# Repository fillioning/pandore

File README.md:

# Pandore

**Open-source digital audio instrument prototyping platform.**

Pandore is a custom-designed PCB built around the [LattePanda Mu](https://www.lattepanda.com/lattepanda-mu) compute module, a [Teensy 4.1](https://www.pjrc.com/store/teensy41.html) audio bridge, dual [RP2350](https://www.raspberrypi.com/products/rp2350/) microcontrollers, and a professional audio I/O chain. It provides a complete hardware foundation for building digital audio instruments, effects processors, and experimental sound tools.

## Status

**Revision A0** — PCBs fabricated (3 units). Manufacturing files released 2026-03-19. DRC passing, all components sourced.

> **PCBWay substitution:** RP2350A was unavailable at assembly time; PCBWay substituted **RP2350B (QFN-80)** for both MCU positions. RP2350A and RP2350B are binary-compatible — same cores, same peripherals, same memory map — they differ only in package size and number of exposed GPIO pins (30 vs 48). Firmware developed on RP2350A Pico boards transfers without modification.

## Board Specifications

| Parameter | Value |
|---|---|
| **Dimensions** | 260 mm x 110 mm |
| **Layers** | 4 (F.Cu / In1 / In2 / B.Cu) |
| **Components** | 804 (141 unique part numbers) |
| **Vias** | 2,217 |
| **Design tool** | KiCad 10 |

## Architecture

```
                         +-----------------+
                         |  LattePanda Mu  |
                         |  (x86-64 SBC)   |
                         +--------+--------+
                                  |
          +----------+-----------+-----------+----------+
          |          |                       |          |
 +--------+-------+  |             +---------+--------+ |
 |  RTIO MCU      |  |             |  Management MCU  | |
 |  (RP2350)      |  |             |  (RP2350)        | |
 +--------+-------+  |             +---------+--------+ |
          |          |                       |          |
 +--------+-------+  |             +---------+--------+ |
 | UART, SPI, I2C |  |             | GPIO, Power Seq, | |
 | ADC, 8x PWM    |  |             | Fan, Display     | |
 +----------------+  |             +------------------+ |
                     |                                  |
            +--------+--------+                         |
            |   Teensy 4.1    |                         |
            | (I2S-to-USB     |                         |
            |  Audio Bridge)  |                         |
            +--------+--------+                         |
                     |                                  |
            +--------+--------+               +---------+--------+
            |   CS4272 Codec  |               |   Boot, BIOS,    |
            |   (24-bit I2S)  |               |   Ethernet, M.2  |
            +-----------------+               +------------------+
```

### Compute

- **LattePanda Mu** — x86-64 SBC (Intel N100 or N305), main application processor. Recommended: DFR1147 (N100, 16 GB LPDDR5) — the N305 gives only ~13% single-core gain at ~2× cost, with no meaningful benefit for real-time audio workloads where single-thread performance dominates.
- **RTIO MCU (RP2350)** — Real-time I/O: UART, SPI, I2C, USB, ADC, 8x PWM channels
- **Management MCU (RP2350)** — System control: power sequencing, GPIO, fan, display, boot

### Audio

- **Audio/MIDI bridge:** [Teensy 4.1](https://www.pjrc.com/store/teensy41.html) — I2S-to-USB audio bridge between the CS4272 codec and the LattePanda Mu, also handles MIDI data transfer to the host computer
- **Codec:** Cirrus Logic CS4272 — stereo 24-bit ADC/DAC, I2S interface
- **Preamp:** THS4521 fully-differential amplifier + OPA1656 op-amp signal conditioning
- **Phantom power:** 48V supply via TI LM5158 flyback controller + TPS7A4001 ultra-low-noise 40V LDO post-regulation (~10 mA) for condenser microphones
- **I2S isolation:** TI ISO7762FDBQR — 6-channel digital isolator (4 forward / 2 reverse), 100 Mbps, 5000 VRMS galvanic isolation between digital and audio domains
- **I2C isolation:** TI ISO1640BDR — isolated I2C for codec control path, 2500 VRMS isolation
- **Isolated power:** Murata NXE2S1212MC — 1W isolated 12V→12V DC/DC converter for the isolated audio domain
- **MIDI isolation:** Isocom H11L1SMT optoisolator with Schmitt-trigger output on MIDI IN
- **Monitor output:** Dedicated headphone/speaker amplifier with hardware volume knob (Bourns PTR902-2020K-A103 — 10 kΩ audio taper, 20 mm shaft)
- **Input buffering:** Balanced input stage with line/mic switching
- **Output buffering:** Line-level outputs

### Power

| Rail | Voltage | Current | Purpose |
|---|---|---|---|
| 12V | Main input | LattePanda Mu, OLED drive |
| 5V | 2A (10W) | Digital logic, USB peripherals |
| 3.3V | 3A (10W) | MCUs, codec digital, I/O |
| 48V | 10 mA | Condenser microphone phantom power |
| AV5 / AV3P3 | — | Analog audio supply (isolated domain) |
| VSTBY | ~3.3V | Standby (CR2032 backup) |

**Power ICs:**

| Part | Role |
|---|---|
| Diodes AP63356Q (×2) | Synchronous buck converters (3.5A), main DC-DC regulation |
| STM LDL212DR (×3) | Ultra-low-dropout LDOs, local clean rails |
| ETEK ET20162 (×5) | Per-rail 5V load switching, 1A each |
| TI LM5158RTER | Flyback controller for 48V phantom supply |
| TI TPS7A4001DGNR | Ultra-low-noise 40V LDO, phantom post-regulation |
| Murata NXE2S1212MC | 1W isolated 12V DC/DC for audio analog domain |

- Reverse-polarity, overcurrent, and overvoltage protection
- PTC fuses (Bel Fuse) on USB VBUS
- Managed power-on sequencing via Management MCU

### Connectivity

- **Ethernet** — 2× Gigabit Ethernet via Realtek RTL8111H-CG PCIe controllers (U7, U8), 2× shielded RJ45 with isolation transformers (Würth 749020111A)
- **USB** — 8× USB from LattePanda Mu (3× USB 3.0 + 5× USB 2.0); 2× USB-C receptacles for Teensy 4.1 bridge
- **MIDI** — 5-pin DIN IN/OUT with H11L1 optoisolation
- **Display** — 24-pin 0.5mm FPC ZIF connector (GCT FFC2A32-24-T) for OLED status display (SSD1309, 128×64 px, 1.54") — see [Components Requiring Separate Assembly](#components-requiring-separate-assembly)
- **M.2 Key-M** — PCIe x4 (NVMe SSD)
- **M.2 Key-A+E** — WiFi/Bluetooth (tested: Intel AX210 — WiFi 6E tri-band + BT 5.3) or alternate storage
- **Expansion headers** — GPIO, analog, I/O breakouts; 2× Grove I2C connectors; I2S header; UART debug

### User Interface

- **Encoder:** Bourns PEL12T-4225T-S1024 — 24 PPR optical rotary encoder with momentary push switch and RGB LED illumination
- **Tactile switches:** 4× C&K PTS810 momentary switches (B1–B4)
- **Volume knob:** Bourns PTR902-2015K-B103 potentiometer (monitor output level)
- **RGBA LED:** AMS-OSRAM multi-colour LEDs — blue (×3), green (×4), orange (×7), red (×1) status/indicator outputs

### Sensors

- **BMI270** — 6-axis IMU (accelerometer + gyroscope) for motion-based control

### Flash Storage

3× Winbond W25Q128JVSIM (128 Mbit / 16 MB, QSPI):
- U2 — BIOS flash (LattePanda Mu)
- U5 — RTIO MCU flash (RP2350, U3)
- U6 — Management MCU flash (RP2350, U4)

### Thermal

- PWM-controlled fan driver circuit
- Three heatsink options: active cooler, thin passive, fanless

## Audio Performance

See **[Audio Performance](AUDIO_PERFORMANCE.md)** for the full signal chain, component specs, system-level estimates, physical I/O, and performance class.

**Highlights:** 24-bit / 192 kHz, 114 dB dynamic range, -100 dB THD+N, 5000 VRMS galvanic isolation, 2× Neutrik combo XLR+TRS inputs with 48V phantom power.

## Repository Structure

```
pandore/
  hw/               Schematics (.kicad_sch) and PCB layout (.kicad_pcb)
  doc/
    arch/           Architecture diagrams (draw.io)
    img/            Board renders
    reference/      Datasheets, app notes, design guides (PDF)
  lib/              3D models (.step), KiCad symbols and footprints
  release/          Manufacturing artifacts (Gerbers, BOM, placement, 3D)
```

### Schematic Hierarchy

The top-level schematic (`pandore.kicad_sch`) references 24 sub-sheets organized by subsystem:

**Audio** — `audio`, `audio-codec`, `audio-inputs`, `audio-inbuf`, `audio-outputs`, `audio-outbuf`, `audio-isolation`, `audio-monitor`, `audio-power`

**Compute** — `computer`, `cpumod`, `mcu`, `mgmtmcu`, `rtmcu`

**Power** — `power`, `audio-power`

**Interface** — `eth`, `usbport`, `midi`, `display`, `extraport`, `mdot2`

**System** — `bootctl`, `bios`, `fan`

## Components Requiring Separate Assembly

The PCBWay PCBA order covers all SMD components. The following through-hole and DNP parts must be sourced and hand-soldered separately. BOM part numbers are listed; substitutions are noted where a different part is recommended over the original BOM.

| BOM# | Per board | Ref | Description | Part (installed) | Notes |
|------|-----------|-----|-------------|-----------------|-------|
| 40 | 1 | E1 | Encoder + RGB LED + switch | Bourns **PEL12T-4225T-S1024** | 24 PPR, push switch, RGB illuminated |
| 47 | 2 | J4, J5 | Mic/Line input combo jack | Neutrik **NCJ9FI-H-0** | XLR + 6.35mm TRS + 3-way switch |
| 50 | 2 | J8, J9 | Ethernet RJ45 | Amphenol **RJE58-188-5411** | 8P8C shielded, dual LEDs, Cat5e |
| 51 | 2 | J10, J11 | MIDI DIN | Same Sky **SDS-50J** | 5-pin DIN 180° |
| 52 | 1 | J12 | Line output TRS | Neutrik **NSJ12HF-1** | 6.35mm stacking stereo |
| 55 | 2 | J15, J16 | GPIO expansion header | Samtec **MTSW-108-22-L-T-330-RA** | 3×8 right-angle, 2.54mm pitch |
| 56 | 2 | J17, J18 | Grove connectors | TE **440055-4** | HPI 2.0mm R/A THT (replaces BOM 2041145-4, same family) |
| 105 | 1 | R273 | Headphone volume pot | Bourns **PTR902-2020K-A103** | Audio taper, 20mm shaft (replaces BOM 2015K-B103, linear, 15mm) |
| — | 1 | J25 | OLED display panel | **Microtips REX012864AYAP3N00000** (primary) or Midas MCOT128064B1V-WM (alt) | SSD1309, 128×64, 24-pin 0.5mm FPC; J25 ZIF socket is PCBWay-assembled |
| — | 1 | J28/J29 | Audio/MIDI bridge module | **PJRC Teensy 4.1** | J28/J29 USB-C receptacles are PCBWay-assembled |
| — | 1 | J13 | NVMe SSD | User choice | M.2 2280 Key-M, PCIe x4 |
| — | 1 | J19 | WiFi/BT module | **Intel AX210** (WiFi 6E + BT 5.3) | M.2 2230 Key-E |

---

## Manufacturing

The `release/` directory contains two packages dated 2026-03-19 (revision A0):

- **`pandore_*_A0_pcba.zip`** — PCBA package: Gerbers, drill files, BOM (.csv), pick-and-place (.pos)
- **`pandore_*_A0_release.zip`** — Full release: PCBA files + 3D assembly model (.step), assembly drawings (PDF), rendered board images, ERC/DRC reports

4-layer stackup. 2,439 drill holes. All components have manufacturer part numbers assigned.

## Reference Documentation

The `doc/reference/` directory includes datasheets and design guides used during development:

- RP2350 datasheet and hardware design guide
- LattePanda Mu evaluation kit guide and carrier board reference
- CS4272 codec (via SuperAudioBoard design guide and schematic)
- THAT1512 microphone preamp gain configuration (reference design)
- 48V phantom power supply design (TI SBOA320A + ultra-low-noise RAQ approach)
- Analog circuit design references (Analog Secrets series, AES mic preamp paper)
- THAT Corporation mic preamp reference design (git submodule)

## Requirements

- [KiCad 10](https://www.kicad.org/) to open and edit schematics and PCB layout
- [draw.io](https://app.diagrams.net/) to view architecture diagrams

## Credits

Designed by **Vincent Fillion** at [Artificiel](https://artificiel.org), with the help of **Alexandre Burton**.

Hardware engineering and KiCad source files by **Laurence Deschênes Villeneuve** ([@laurencedv](https://github.com/laurencedv)).

## License

This project is licensed under the [CERN Open Hardware Licence Version 2 — Strongly Reciprocal (CERN-OHL-S-2.0)](https://ohwr.org/cern_ohl_s_v2.txt).

You are free to use, study, modify, and distribute this design, provided that:
- You credit the original authors
- You distribute any modified versions under the same licence
- You make the source files available

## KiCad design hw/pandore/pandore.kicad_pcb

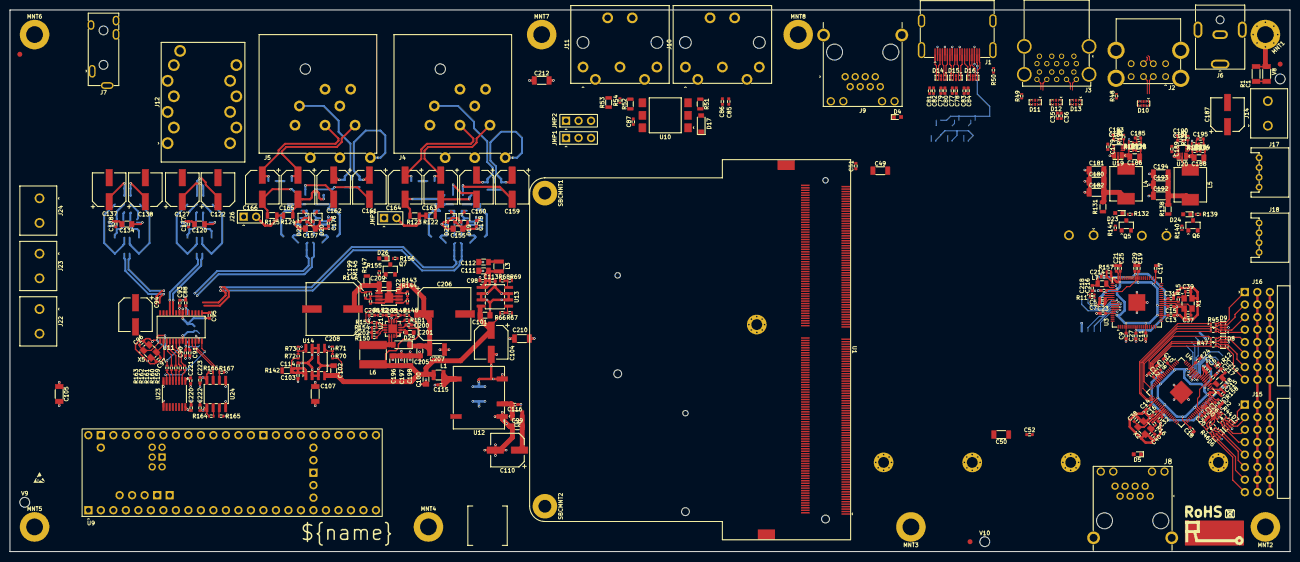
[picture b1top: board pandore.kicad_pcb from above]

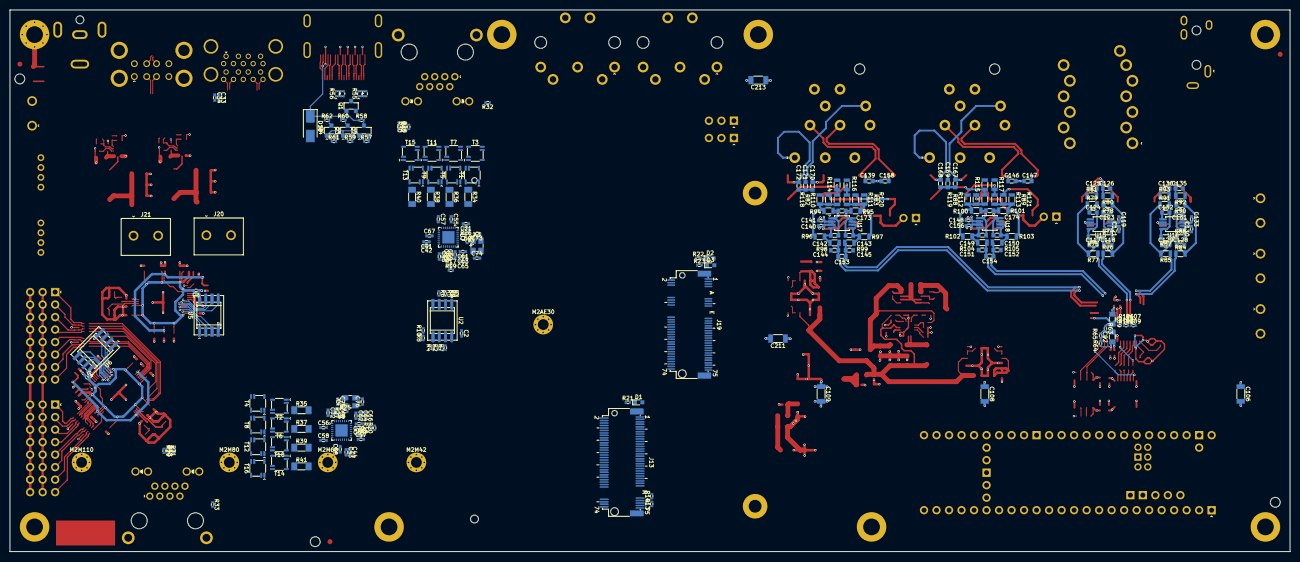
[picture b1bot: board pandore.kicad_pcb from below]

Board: 4 copper layers, 260.0 x 110.0 mm, 530 parts (227 on the bottom side), 432 nets.

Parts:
C1: 10nF, 630V, X7R; CAPC3216
C2, C3, C4, C5, C6, C7, C8, C9, C10, C11, C12, C13, C14, C15, C16, C17, C18, C19, C20, C21, C22, C23, C24, C25, C26, C27, C28, C29, C30, C33, C34, C35, C36, C41, C42, C43, C44, C45, C46, C47, C48, C51, C52, C53, C54, C55, C56, C57, C58, C59, C60, C61, C62, C67, C68, C69, C70, C71, C72, C77, C78, C79, C80, C81, C82, C83, C84, C85, C86, C87, C88, C90, C91, C93, C95, C113, C114, C119, C133, C140, C156, C175, C176, C177, C178, C179, C189, C220, C221, C222, C223: 100nF, 16V, X7R; CAPC1005
C31, C32, C63, C64, C65, C66, C98, C103, C214, C215, C216, C217, C218, C219: 4.7µF, 6.3V, X5R; CAPC1005
C37, C38, C39, C40: 15pF, 6.3V, X7R; CAPC1005
C49, C50: 1nF, 1000V, X7R; CAPC3216
C73, C74, C75, C76, C96, C97: 12pF, 6.3V, X7R; CAPC1005
C89, C92: 10µF, 16V, X5R; CAPC2012
C94, C104, C110: 47µF, 25V, 20%; CAPAE630Xxxx
C99, C100, C101, C102, C111, C112, C120, C134, C155, C157, C186, C188, C196, C197, C198: 10µF, 25V, X5R; CAPC2012
C105, C106, C107, C108, C109, C210, C211, C212, C213: 100pF, 1kV, X5R; CAPC3216
C115, C116, C200: 100nF, 25V, X7R; CAPC1005
C117, C118, C128, C129: 1.3nF, 16V, C0G; CAPC1608
C121, C130, C141, C148: 220nF, 16V, X7R; CAPC1005
C122, C127, C137, C138, C159, C160, C161, C162, C187: 100µF, 25V, 20%; CAPAE630Xxxx
C123, C124, C131, C132: 300pF, 16V, C0G; CAPC1608
C125, C126, C135, C136: 33nF, 16V, C0G; CAPC1608
C139, C144, C145, C146, C147, C151, C152, C158, C167, C168, C169, C170, C171, C172, C173, C174: 100pF, 50V, C0G; CAPC1608
C142, C143, C149, C150: 1nF, 16V, C0G; CAPC1608
C153, C154: 2.7nF, 16V, C0G; CAPC1608
C163, C164, C165, C166: 47µF, 100V, 20%; CAPAE630Xxxx
C180, C181, C182, C192, C193, C194: 22µF, 25V, X5R; CAPC3216
C183, C190, C204: 1nF, 16V, X7R; CAPC1005
C184, C191: 68pF, 10V, X7R; CAPC1005
C185, C195: 47pF, 10V, X7R; CAPC1005
C199: 10nF, 100V, X7R; CAPC1005
C201: 1µF, 16V, X7R; CAPC1608
C202: 12nF, 16V, X7R; CAPC1005
C203: 1pF, 16V, X7R; CAPC1005
C205, C209: 100nF, 100V, X7R; CAPC2012
C206, C208: 56µF, 100V, 20%; CAPAE1000Xxxx
C207: 10µF, 100V, X5R; CAPC3225
D1, D2, D3, D4, D5, D23, D24, D26: green; LEDM1608X80
D6, D7, D8, D9, D10, D11, D12, D13, D14, D15, D16: 5V; DFN50P100X250X55-10_ESD204
D17: 75V, 150mA, 1V@100mA; sod-123
D18: 40V, 3A, 500mV@3A; dio_sma
D19, D20, D21, D22: 75V, 140mA, 1.25V@150mA; SOT65P210X90-3
D25: 100V, 150mA, 450mV@10mA; sod-123
J1: HDMI; te_1747981-1
J2: USB2-A_2stacked; USB2_A_RCPT_HORZ_2STACKED
J3: USB3-A_2stacked; USB3_A_RCPT_HORZ_2STACKED
J4, J5: XLR+TRS6.35+3SW; neutrik_ncj9fi-h-0
J6: VIN; samesky_PJ-063BH
J7: TRS; samesky_SJ3-3508x
J8, J9: 8p8c_2led_shield; amphenol_RJE58-188-54x1-0x
J10: MIDI_in; samesky_SDS-50J
J11: MIDI_out; samesky_SDS-50J
J12: TRS; neutrik_nsj12hf-1
J13: NGFF_M.2_M; NGFF_M.2_CONN
J14: VIN; Wurth_691137710002
J15: AIO; HDR254P3X8-THRA
J16: DIO; HDR254P3X8-THRA
J17, J18: GROVE; te_2041145-4
J19: NGFF_M.2_AE; NGFF_M.2_CONN
J20: V5; Wurth_691137710002
J21: V3.3; Wurth_691137710002
J22: V12ISO; Wurth_691137710002
J23: AV5; Wurth_691137710002
J24: AV3P3; Wurth_691137710002
J26: PPWR; HDR254P1X02-TH
JMP1: MIDIRX; HDR254P1X03-TH
JMP2: MIDITX; HDR254P1X03-TH
JMP3: PPWR; HDR254P1X02-TH
L1, L2, L3: 10µH; INDC2520
L4, L5: 8.2µH, 5A; Eaton_HPAL1V0630
L6: Ind; WE_IND5030
L7, L8: 3.3µH, 1.8A; INDC2012
M2AE30, M2M42, M2M60, M2M80, M2M110: M2; mnt_M2_ele
MNT1: MNT-CHASSIS; mnt_M3_ele
MNT2, MNT3, MNT4, MNT5, MNT6, MNT7, MNT8: Mounting; mnt_M3
Q1, Q2, Q3, Q4, Q5, Q6, Q7: MOSFET_EN-N; SOT95P280X100-3
R1: 1MΩ, 5%, 250mW; RESC3216
R2, R3, R4, R5, R6, R7: 0, 5%, 63mW; RESC1005
R8, R9, R10, R13, R17, R18, R19, R20, R64, R66, R67, R68, R69, R70, R71, R72, R73, R106, R107, R108, R109, R129, R130, R133, R134, R140, R141, R143, R144, R145, R146, R155: 10kΩ, 1%, 63mW; RESC1005
R11, R12: 27Ω, 5%, 63mW; RESCAXSR65P100X100X35-4
R14, R15, R16, R21, R22, R23, R42, R43, R65, R132, R139, R156: 1kΩ, 1%, 63mW; RESC1005
R24, R25: 1MΩ, 1%, 63mW; RESC1005
R26, R27: 2.49kΩ, 1%, 63mW; RESC1005
R28, R29, R30, R31: 470Ω, 1%, 63mW; RESC1005
R32, R33, R48, R49, R50, R54, R63: 0Ω, 5%, 63mW; RESC1005
R34, R35, R36, R37, R38, R39, R40, R41: 75Ω, 1%, 250mW; RESMELF0204
R44, R45, R46, R47, R55, R56: 560Ω, 5%, 63mW; RESCAXSR50P200X100X35-8
R51: 220Ω, 1%, 250mW; RESC2012
R52: 10Ω, 1%, 250mW; RESC2012
R53: 33Ω, 1%, 250mW; RESC2012
R57, R58, R59, R60, R61, R62, R164, R165, R166, R167: 2.2kΩ, 1%, 63mW; RESC1005
R74, R75, R76, R77, R78, R79, R84, R85, R86, R87, R90, R91: 5.1kΩ, 0.5%, thin film; RESC2012
R80, R81, R92, R93: 100Ω, 1%, thin film; RESC2012
R82, R83, R88, R89: 10Ω, 1%, thin film; RESC2012
R94, R95, R96, R97, R100, R101, R102, R103, R118, R119, R120, R121: 1kΩ, 0.5%, thin film; RESC2012
R98, R99, R104, R105: 40.2Ω, 1%, thin film; RESC2012
R110, R112: 9.09kΩ, 0.5%, thin film; RESC2012
R111, R113: 9.01kΩ, 0.5%, thin film; RESC2012
R114, R115, R116, R117: 47kΩ, 0.5%, thin film; RESC2012
R122, R123, R124, R125: 6.8kΩ, 0.5%, thin film; RESC2012
R126: 158kΩ, 1%, 63mW; RESC1005
R127, R137: 30kΩ, 1%, 63mW; RESC1005
R128: 68.1kΩ, 1%, 63mW; RESC1005
R131, R138, R142, R147: 0Ω, 5%, thin film; RESC2012
R135: 100kΩ, 1%, 63mW; RESC1005
R136: 93.1kΩ, 1%, 63mW; RESC1005
R148, R153: 316kΩ, 1%, 63mW; RESC1005
R149, R154: 53.6kΩ, 1%, 63mW; RESC1005
R150: 37.4kΩ, 1%, 63mW; RESC1005
R151: 21kΩ, 1%, 63mW; RESC1005
R152: 105kΩ, 1%, 63mW; RESC1005
R157, R158: 33Ω, 1%, 63mW; RESC1005
R159, R160, R161, R162, R163: 49.9Ω, 1%, 63mW; RESC1005
SBCMNT1: SBC-CHASSIS; spacer_M2
SBCMNT2: Mounting; spacer_M2
T1, T2, T3, T4, T5, T6, T7, T8, T9, T10, T11, T12, T13, T14, T15, T16: tran_choke_center; TDK_ALT3232M
U1: LattePanda_Mu; LattePanda_Module_H8.0mm_Horizontal
U2, U5, U6: mem_flash_spi; SOIC127PxxxX200-8
U3, U4: RP2350B; QFN40P1000X1000-81
U7, U8: RTL8111H; QFN40P400X400-33
U9: Teensy 4.1; teensy_4.1
U10: H11L1; SOIC254P1030X430-6
U11: CS4272; SOP65P640X970-28
U12: NXES2; murata_nxe2
U13, U14: LDL212DR; SOIC127P600X150-8
U15, U16, U17, U18: OPAMP_DIFF_1; SOP65P490X300-8
U19, U20: AP6335xQ; DFN300X200X90-9
U21: LM5158; QFN50P300X300-17
U22: TPS7A4001; SOP65P490X300-9
U23: ISO7762; SOP635P600X490-16
U24: ISO1640; SOIC127P600X150-8
V1: realee logo; logo_realee_5mm
V2: rohs icon; icon_rohs_
V3: notrash icon; icon_notrash
V4: esd icon; icon_esdwarning_3mm
V5, V6, V7: fiducial; fiducial_1to2_1mm
V8, V9, V10: tooling hole; mechole_2.0mm
V11: serial; serial_8x8
X1, X2: 12MHz, 30ppm+30ppm, 10pF; OSCCC320X250X90
X3, X4: 25MHz, 30ppm+30ppm, 10pF; OSCCC320X250X90
X5: 24.576MHz, 50ppm+20ppm, 18pF; OSCCC320X250X90

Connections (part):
/Audio/AUDMST.SCL: R165.2, U9.41 (I2C0.SCL), U24.3 (SCL1)
/Audio/AUDMST.SDA: R164.2, U9.40 (I2C0.SDA), U24.2 (SDA1)
/Audio/Audio inputs/IN buffer 1/INBUF.FB+: R82.2, R94.1, R96.1, R110.2, R118.2
/Audio/Audio inputs/IN buffer 1/INBUF.FB-: R83.2, R95.1, R97.1, R111.2, R120.2
/Audio/Audio inputs/IN buffer 1/INBUF.IN+: C142.2, C173.2, D19.3 (M), R94.2, U17.1 (IN-)
/Audio/Audio inputs/IN buffer 1/INBUF.IN-: C143.2, C173.1, D21.3 (M), R95.2, U17.8 (IN+)
/Audio/Audio inputs/IN buffer 1/INBUF.OUT+: C142.1, R96.2, R98.1, U17.4 (OUT+)
/Audio/Audio inputs/IN buffer 1/INBUF.OUT-: C143.1, R97.2, R99.1, U17.5 (OUT-)
/Audio/Audio inputs/IN buffer 2/INBUF.FB+: R88.2, R100.1, R102.1, R112.2, R119.2
/Audio/Audio inputs/IN buffer 2/INBUF.FB-: R89.2, R101.1, R103.1, R113.2, R121.2
/Audio/Audio inputs/IN buffer 2/INBUF.IN+: C149.2, C174.2, D20.3 (M), R100.2, U18.1 (IN-)
/Audio/Audio inputs/IN buffer 2/INBUF.IN-: C150.2, C174.1, D22.3 (M), R101.2, U18.8 (IN+)
/Audio/Audio inputs/IN buffer 2/INBUF.OUT+: C149.1, R102.2, R104.1, U18.4 (OUT+)
/Audio/Audio inputs/IN buffer 2/INBUF.OUT-: C150.1, R103.2, R105.1, U18.5 (OUT-)
/Audio/Audio inputs/LINE1IN.SIG+: C159.2 (-), R110.1, R114.2
/Audio/Audio inputs/LINE1IN.SIG-: C160.2 (-), R111.1, R116.2
/Audio/Audio inputs/LINE2IN.SIG+: C161.2 (-), R112.1, R115.2
/Audio/Audio inputs/LINE2IN.SIG-: C162.2 (-), R113.1, R117.2
/Audio/Audio inputs/MIC1IN.SIG+: C163.2 (-), R82.1, R122.1
/Audio/Audio inputs/MIC1IN.SIG-: C164.2 (-), R83.1, R123.1
/Audio/Audio inputs/MIC2IN.SIG+: C165.2 (-), R88.1, R124.1
/Audio/Audio inputs/MIC2IN.SIG-: C166.2 (-), R89.1, R125.1
/Audio/Audio inputs/MICLINE1.SIG+: C144.1, C153.2, R98.2, U11.17 (AINA+)
/Audio/Audio inputs/MICLINE1.SIG-: C145.2, C153.1, R99.2, U11.16 (AINA-)
/Audio/Audio inputs/MICLINE2.SIG+: C151.1, C154.2, R104.2, U11.18 (AINB+)
/Audio/Audio inputs/MICLINE2.SIG-: C152.2, C154.1, R105.2, U11.19 (AINB-)
/Audio/Audio inputs/VCM: C95.2, C121.2, C130.2, C141.2, C148.2, U11.15 (VCOM), U15.2 (VCOM), U16.2 (VCOM), U17.2 (VCOM), U18.2 (VCOM)
/Audio/Audio inputs/_LINE1IN.SIG+: C159.1 (+), C172.2, J4.T
/Audio/Audio inputs/_LINE1IN.SIG-: C160.1 (+), C170.2, J4.R
/Audio/Audio inputs/_LINE2IN.SIG+: C161.1 (+), C168.2, J5.T
/Audio/Audio inputs/_LINE2IN.SIG-: C162.1 (+), C167.2, J5.R
/Audio/Audio inputs/_MIC1IN.SIG+: C139.1, C163.1 (+), J4.2
/Audio/Audio inputs/_MIC1IN.SIG-: C158.2, C164.1 (+), J4.3
/Audio/Audio inputs/_MIC2IN.SIG+: C146.1, C165.1 (+), J5.2
/Audio/Audio inputs/_MIC2IN.SIG-: C147.2, C166.1 (+), J5.3
/Audio/Audio inputs/~MUTE.L: R106.2, R107.1, U11.23 (~AMUTEC), U15.7 (~PD), U17.7 (~PD)
/Audio/Audio inputs/~MUTE.R: R108.2, R109.1, U11.28 (~BMUTEC), U16.7 (~PD), U18.7 (~PD)
/Audio/Audio outputs/LEFT.SIG+: R76.1, U11.25 (AOUTA+)
/Audio/Audio outputs/LEFT.SIG-: R77.1, U11.24 (AOUTA-)
/Audio/Audio outputs/OUT buffer L/OUT+: C122.1 (+), C126.1, R80.2
/Audio/Audio outputs/OUT buffer L/OUT-: C125.2, C127.1 (+), R81.2
/Audio/Audio outputs/OUT buffer L/OUTBUF.FB+: C118.1, R74.1, R76.2, R78.1
/Audio/Audio outputs/OUT buffer L/OUTBUF.FB-: C117.2, R75.1, R77.2, R79.1
/Audio/Audio outputs/OUT buffer L/OUTBUF.IN+: C123.2, R74.2, U15.1 (IN-)
/Audio/Audio outputs/OUT buffer L/OUTBUF.IN-: C124.2, R75.2, U15.8 (IN+)
/Audio/Audio outputs/OUT buffer L/OUTBUF.OUT+: C123.1, R78.2, R80.1, U15.4 (OUT+)
/Audio/Audio outputs/OUT buffer L/OUTBUF.OUT-: C124.1, R79.2, R81.1, U15.5 (OUT-)
/Audio/Audio outputs/OUT buffer R/OUT+: C135.1, C137.1 (+), R92.2
/Audio/Audio outputs/OUT buffer R/OUT-: C136.2, C138.1 (+), R93.2
/Audio/Audio outputs/OUT buffer R/OUTBUF.FB+: C128.1, R84.2, R86.1, R90.1
/Audio/Audio outputs/OUT buffer R/OUTBUF.FB-: C129.2, R85.2, R87.1, R91.1
/Audio/Audio outputs/OUT buffer R/OUTBUF.IN+: C131.2, R86.2, U16.1 (IN-)
/Audio/Audio outputs/OUT buffer R/OUTBUF.IN-: C132.2, R87.2, U16.8 (IN+)
/Audio/Audio outputs/OUT buffer R/OUTBUF.OUT+: C131.1, R90.2, R92.1, U16.4 (OUT+)
/Audio/Audio outputs/OUT buffer R/OUTBUF.OUT-: C132.1, R91.2, R93.1, U16.5 (OUT-)
/Audio/Audio outputs/OUTL.SIG+: C122.2 (-), J12.SB
/Audio/Audio outputs/OUTL.SIG-: C127.2 (-), J12.RB
/Audio/Audio outputs/OUTR.SIG+: C137.2 (-), J12.ST
/Audio/Audio outputs/OUTR.SIG-: C138.2 (-), J12.RT
/Audio/Audio outputs/RIGHT.SIG+: R84.1, U11.26 (AOUTB+)
/Audio/Audio outputs/RIGHT.SIG-: R85.1, U11.27 (AOUTB-)
/Audio/CODEC/CTL.SCL: R167.2, U11.12 (SDA), U24.6 (SCL2)
/Audio/CODEC/CTL.SDA: R166.2, U11.11 (SCL), U24.7 (SDA2)
/Audio/CODEC/DATA.MCLK: R162.2, U11.3 (MCLK)
/Audio/CODEC/DATA.RXD0: R159.2, U11.6 (SDOUT)
/Audio/CODEC/DATA.TXCLK: R160.2, U11.5 (SCLK)
/Audio/CODEC/DATA.TXD0: R163.2, U11.7 (SDIN)
/Audio/CODEC/DATA.TXFS: R161.2, U11.4 (LRCK)
/Audio/CODEC/~RST: U11.14 (~RST), U23.7 (OUTF)
/Audio/MIDI.RX: JMP1.1, U9.26 (UART8.RX)
/Audio/MIDI.TX: JMP2.1, U9.27 (UART8.TX)
/Audio/Power/REGV48.OUT: C199.2, C208.1 (+), C209.2, R145.1, R147.1, U22.1 (OUT)
/Audio/USB.D+: U1.112 (USB2_P6+), U9.56 (USBH.D+)
/Audio/USB.D-: U1.114 (USB2_P6-), U9.55 (USBH.D-)
/Computer/AUDIO.MIDI.RX: JMP1.3, U1.140 (UART2_RXD)
/Computer/AUDIO.MIDI.TX: JMP2.3, U1.138 (UART2_TXD)
/Computer/BIOS mem/BIOS.IO0: R4.1, U1.159 (SPI_MOSI/SPI_IO0)
/Computer/BIOS mem/BIOS.IO1: R5.1, U1.163 (SPI_MISO/SPI_IO1)
/Computer/BIOS mem/BIOS.IO2: R6.1, U1.161 (SPI_IO2)
/Computer/BIOS mem/BIOS.IO3: R7.1, U1.153 (SPI_IO3)
/Computer/BIOS mem/BIOS.SCK: R2.1, U1.155 (SPI_CLK)
/Computer/BIOS mem/BIOS.SEL: R8.2, R10.1, U1.133 (~BIOS_SEL)
/Computer/BIOS mem/BIOS.~SS: R3.1, R9.2, U1.165 (~SPI_CS)
/Computer/BIOS mem/BIOSMEM.IO0: R4.2, U2.5 (IO0)
/Computer/BIOS mem/BIOSMEM.IO1: R5.2, U2.2 (IO1)
/Computer/BIOS mem/BIOSMEM.IO2: R6.2, U2.3 (IO2)
/Computer/BIOS mem/BIOSMEM.IO3: R7.2, U2.7 (IO3)
/Computer/BIOS mem/BIOSMEM.SCK: R2.2, U2.6 (SCK)
/Computer/BIOS mem/BIOSMEM.~SS: R3.2, U2.1 (~CS)
/Computer/DDIB.CLK+: C83.2, U1.199 (DDIB_TX3+)
/Computer/DDIB.CLK-: C84.2, U1.197 (DDIB_TX3-)
/Computer/DDIB.D0+: C77.2, U1.205 (DDIB_TX2+)
/Computer/DDIB.D0-: C78.2, U1.203 (DDIB_TX2-)
/Computer/DDIB.D1+: C79.2, U1.211 (DDIB_TX1+)
/Computer/DDIB.D1-: C80.2, U1.209 (DDIB_TX1-)
/Computer/DDIB.D2+: C81.2, U1.217 (DDIB_TX0+)
/Computer/DDIB.D2-: C82.2, U1.215 (DDIB_TX0-)
/Computer/DDIB.DDC.CLK: Q2.2 (S), R57.2, U1.171 (DDIB_DDC_SCL)
/Computer/DDIB.DDC.DAT: Q3.2 (S), R59.2, U1.169 (DDIB_DDC_SDA)
/Computer/DDIB.HPD: Q4.2 (S), R61.2, U1.183 (DDIB_HPD)
/Computer/ETHI.HSI0+: C47.2, U1.28 (HSIO2_RX+)
/Computer/ETHI.HSI0-: C48.2, U1.30 (HSIO2_RX-)
/Computer/ETHI.HSO0+: C43.2, U1.25 (HSIO2_TX+)
/Computer/ETHI.HSO0-: C44.2, U1.27 (HSIO2_TX-)
/Computer/ETHI.REFCLK+: U1.85 (REFCLK0+), U8.15 (REFCLK+)
/Computer/ETHI.REFCLK-: U1.87 (REFCLK0-), U8.16 (REFCLK-)
/Computer/ETHI.~WAKE: R18.1, U8.21 (~LANWAKE)
/Computer/ETHX.HSI0+: C45.2, U1.64 (HSIO6_RX+)
/Computer/ETHX.HSI0-: C46.2, U1.66 (HSIO6_RX-)
/Computer/ETHX.HSO0+: C41.2, U1.61 (HSIO6_TX+)
/Computer/ETHX.HSO0-: C42.2, U1.63 (HSIO6_TX-)
/Computer/ETHX.REFCLK+: U1.94 (REFCLK4+), U7.15 (REFCLK+)
/Computer/ETHX.REFCLK-: U1.96 (REFCLK4-), U7.16 (REFCLK-)
/Computer/ETHX.~WAKE: R17.1, U7.21 (~LANWAKE)
/Computer/M2E.HSI0+: J19.35 (PE.HRX0+), U1.34 (HSIO3_RX+)
/Computer/M2E.HSI0-: J19.37 (PE.HRX0-), U1.36 (HSIO3_RX-)
/Computer/M2E.HSO0+: J19.41 (PE.HTX0+), U1.31 (HSIO3_TX+)
/Computer/M2E.HSO0-: J19.43 (PE.HTX0-), U1.33 (HSIO3_TX-)
/Computer/M2E.REFCLK+: J19.47 (PE.REFCLK0+), U1.88 (REFCLK3+)
/Computer/M2E.REFCLK-: J19.49 (PE.REFCLK0-), U1.90 (REFCLK3-)
/Computer/M2M.HSI0+: J13.43 (PE.HRX0+), U1.40 (HSIO8_RX+)
/Computer/M2M.HSI0-: J13.41 (PE.HRX0-), U1.42 (HSIO8_RX-)
/Computer/M2M.HSI1+: J13.31 (PE.HRX1+), U1.46 (HSIO9_RX+)
/Computer/M2M.HSI1-: J13.29 (PE.HRX1-), U1.48 (HSIO9_RX-)
/Computer/M2M.HSI2+: J13.19 (PE.HRX2+), U1.52 (HSIO10_RX+)
/Computer/M2M.HSI2-: J13.17 (PE.HRX2-), U1.54 (HSIO10_RX-)
/Computer/M2M.HSI3+: J13.7 (PE.HRX3+), U1.58 (HSIO11_RX+)
/Computer/M2M.HSI3-: J13.5 (PE.HRX3-), U1.60 (HSIO11_RX-)
/Computer/M2M.HSO0+: J13.49 (PE.HTX0+), U1.37 (HSIO8_TX+)
/Computer/M2M.HSO0-: J13.47 (PE.HTX0-), U1.39 (HSIO8_TX-)
/Computer/M2M.HSO1+: J13.37 (PE.HTX1+), U1.43 (HSIO9_TX+)
/Computer/M2M.HSO1-: J13.35 (PE.HTX1-), U1.45 (HSIO9_TX-)
/Computer/M2M.HSO2+: J13.25 (PE.HTX2+), U1.49 (HSIO10_TX+)
/Computer/M2M.HSO2-: J13.23 (PE.HTX2-), U1.51 (HSIO10_TX-)
/Computer/M2M.HSO3+: J13.13 (PE.HTX3+), U1.55 (HSIO11_TX+)
/Computer/M2M.HSO3-: J13.11 (PE.HTX3-), U1.57 (HSIO11_TX-)
/Computer/M2M.REFCLK+: J13.55 (PE.REFCLK+), U1.97 (REFCLK2+)
/Computer/M2M.REFCLK-: J13.53 (PE.REFCLK-), U1.99 (REFCLK2-)
/Computer/USB2P3.D+: D10.4, J2.7 (BOT_D+), U1.81 (USB2_P3+)
/Computer/USB2P3.D-: D10.5, J2.6 (BOT_D-), U1.79 (USB2_P3-)
/Computer/USB2P4.D+: R11.2, U1.70 (USB2_P4+)
/Computer/USB2P4.D-: R11.1, U1.72 (USB2_P4-)
/Computer/USB2P5.D+: D10.1, J2.3 (TOP_D+), U1.111 (USB2_P5+)
/Computer/USB2P5.D-: D10.2, J2.2 (TOP_D-), U1.109 (USB2_P5-)
/Computer/USB2P7.D+: J19.3 (USB.D+), U1.76 (USB2_P7+)
/Computer/USB2P7.D-: J19.5 (USB.D-), U1.78 (USB2_P7-)
/Computer/USB2P8.D+: R12.2, U1.82 (USB2_P8+)
/Computer/USB2P8.D-: R12.1, U1.84 (USB2_P8-)
/Computer/USB3P2.D+: D13.2, J3.3 (BOT_D+), U1.75 (USB2_P2+)
/Computer/USB3P2.D-: D13.1, J3.2 (BOT_D-), U1.73 (USB2_P2-)
/Computer/USB3P2.SSRX+: D11.4, J3.6 (BOT_SSRX+), U1.16 (HSIO0_RX+)
/Computer/USB3P2.SSRX-: D11.5, J3.5 (BOT_SSRX-), U1.18 (HSIO0_RX-)
/Computer/USB3P2.SSTX+: C34.2, U1.13 (HSIO0_TX+)
/Computer/USB3P2.SSTX-: C33.2, U1.15 (HSIO0_TX-)
/Computer/USBP1.D+: D13.4, J3.12 (TOP_D+), U1.69 (USB2_P1+)
/Computer/USBP1.D-: D13.5, J3.11 (TOP_D-), U1.67 (USB2_P1-)
/Computer/USBP1.SSRX+: D12.4, J3.15 (TOP_SSRX+), U1.22 (HSIO1_RX+)
/Computer/USBP1.SSRX-: D12.5, J3.14 (TOP_SSRX-), U1.24 (HSIO1_RX-)
/Computer/USBP1.SSTX+: C36.2, U1.19 (HSIO1_TX+)
/Computer/USBP1.SSTX-: C35.2, U1.21 (HSIO1_TX-)
/Display/_HDMI.CLK+: C83.1, D15.2, J1.10 (TMDS.CLK+), R56.7
/Display/_HDMI.CLK-: C84.1, D15.1, J1.12 (TMDS.CLK-), R56.8
/Display/_HDMI.D0+: C77.1, D15.5, J1.7 (TMDS.D0+), R56.5
/Display/_HDMI.D0-: C78.1, D15.4, J1.9 (TMDS.D0-), R56.6
/Display/_HDMI.D1+: C79.1, D14.2, J1.4 (TMDS.D1+), R55.7
/Display/_HDMI.D1-: C80.1, D14.1, J1.6 (TMDS.D1-), R55.8
/Display/_HDMI.D2+: C81.1, D14.5, J1.1 (TMDS.D2+), R55.5
/Display/_HDMI.D2-: C82.1, D14.4, J1.3 (TMDS.D2-), R55.6
/External Ethernet/ETH.VCORE: C53.2, C55.2, C57.2, C59.2, C61.2, C63.2, C65.2, U7.3 (AVDD10), U7.8 (AVDD10), U7.22 (DVDD10), U7.24 (REGOUT), U7.30 (AVDD10)
/External Ethernet/ETH.VIO: C67.2, C69.2, C71.2, R17.2, R19.2, R28.1, R30.1, R42.2, U7.11 (AVDD33), U7.23 (VDDREG), U7.32 (AVDD33)
/External Ethernet/ETHPCIE.RX+: C41.1, U7.13 (HSI(PCIE.RX)+)
/External Ethernet/ETHPCIE.RX-: C42.1, U7.14 (HSI(PCIE.RX)-)
/External Ethernet/ETHPCIE.TX+: C45.1, U7.17 (HSO(PCIE.TX)+)
/External Ethernet/ETHPCIE.TX-: C46.1, U7.18 (HSO(PCIE.TX)-)
/External Ethernet/MDI0+: T1.1, U7.1 (MDI0+)
/External Ethernet/MDI0-: T1.2, U7.2 (MDI0-)
/External Ethernet/MDI1+: T5.1, U7.4 (MDI1+)
/External Ethernet/MDI1-: T5.2, U7.5 (MDI1-)
/External Ethernet/MDI2+: T9.1, U7.6 (MDI2+)
/External Ethernet/MDI2-: T9.2, U7.7 (MDI2-)
/External Ethernet/MDI3+: T13.1, U7.9 (MDI3+)
/External Ethernet/MDI3-: T13.2, U7.10 (MDI3-)
/External Ethernet/PAIR0+: J9.1 (C1), T3.4
/External Ethernet/PAIR0-: J9.2 (C2), T3.2
/External Ethernet/PAIR1+: J9.3 (C3), T7.4
/External Ethernet/PAIR1-: J9.4 (C4), T7.2
/External Ethernet/PAIR2+: J9.5 (C5), T11.4
/External Ethernet/PAIR2-: J9.6 (C6), T11.2
/External Ethernet/PAIR3+: J9.7 (C7), T15.4
/External Ethernet/PAIR3-: J9.8 (C8), T15.2
/External Ethernet/_MDI0+: T1.5, T3.5
/External Ethernet/_MDI0-: T1.4, T3.1
/External Ethernet/_MDI1+: T5.5, T7.5
/External Ethernet/_MDI1-: T5.4, T7.1
/External Ethernet/_MDI2+: T9.5, T11.5
/External Ethernet/_MDI2-: T9.4, T11.1
/External Ethernet/_MDI3+: T13.5, T15.5
/External Ethernet/_MDI3-: T13.4, T15.1
/Internal Ethernet/ETH.VCORE: C54.2, C56.2, C58.2, C60.2, C62.2, C64.2, C66.2, U8.3 (AVDD10), U8.8 (AVDD10), U8.22 (DVDD10), U8.24 (REGOUT), U8.30 (AVDD10)
/Internal Ethernet/ETH.VIO: C68.2, C70.2, C72.2, R18.2, R20.2, R29.1, R31.1, R43.2, U8.11 (AVDD33), U8.23 (VDDREG), U8.32 (AVDD33)
/Internal Ethernet/ETHPCIE.RX+: C43.1, U8.13 (HSI(PCIE.RX)+)
/Internal Ethernet/ETHPCIE.RX-: C44.1, U8.14 (HSI(PCIE.RX)-)
/Internal Ethernet/ETHPCIE.TX+: C47.1, U8.17 (HSO(PCIE.TX)+)
/Internal Ethernet/ETHPCIE.TX-: C48.1, U8.18 (HSO(PCIE.TX)-)
/Internal Ethernet/MDI0+: T2.1, U8.1 (MDI0+)
/Internal Ethernet/MDI0-: T2.2, U8.2 (MDI0-)
/Internal Ethernet/MDI1+: T6.1, U8.4 (MDI1+)
/Internal Ethernet/MDI1-: T6.2, U8.5 (MDI1-)
/Internal Ethernet/MDI2+: T10.1, U8.6 (MDI2+)
/Internal Ethernet/MDI2-: T10.2, U8.7 (MDI2-)
/Internal Ethernet/MDI3+: T14.1, U8.9 (MDI3+)
/Internal Ethernet/MDI3-: T14.2, U8.10 (MDI3-)
/Internal Ethernet/PAIR0+: J8.1 (C1), T4.4
/Internal Ethernet/PAIR0-: J8.2 (C2), T4.2
/Internal Ethernet/PAIR1+: J8.3 (C3), T8.4
/Internal Ethernet/PAIR1-: J8.4 (C4), T8.2
/Internal Ethernet/PAIR2+: J8.5 (C5), T12.4
/Internal Ethernet/PAIR2-: J8.6 (C6), T12.2
/Internal Ethernet/PAIR3+: J8.7 (C7), T16.4
/Internal Ethernet/PAIR3-: J8.8 (C8), T16.2
/Internal Ethernet/_MDI0+: T2.5, T4.5
/Internal Ethernet/_MDI0-: T2.4, T4.1
/Internal Ethernet/_MDI1+: T6.5, T8.5
/Internal Ethernet/_MDI1-: T6.4, T8.1
/Internal Ethernet/_MDI2+: T10.5, T12.5
/Internal Ethernet/_MDI2-: T10.4, T12.1
/Internal Ethernet/_MDI3+: T14.5, T16.5
/Internal Ethernet/_MDI3-: T14.4, T16.1
/MIDI/MIDI.RX: JMP1.2, U10.4 (Vo)
/MIDI/MIDI.TX: JMP2.2, R52.2
/Mgmt MCU/GROVEA.PRIM: J17.1 (SCL), U3.52 (GPIO41~(PD)|F2:UART1.RX)
/Mgmt MCU/GROVEA.SEC: J17.2 (SDA), U3.49 (GPIO40~(PD)|F3:I2C0.SDA)
/Mgmt MCU/GROVEB.PRIM: J18.1 (SCL), U3.48 (GPIO39¹(PD)|F3:I2C1.SCL), U3.56 (GPIO45~(PD)|F2:UART0.RX)
/Mgmt MCU/GROVEB.SEC: J18.2 (SDA), U3.47 (GPIO38¹(PD)|F3:I2C1.SDA), U3.55 (GPIO44~(PD)|F2:UART0.TX)
/Mgmt MCU/MCU/QSPI.D0: U3.72 (QSPI.SD0(PD)|F0:QMI.SD0), U5.5 (IO0)
/Mgmt MCU/MCU/QSPI.D1: U3.74 (QSPI.SD1²(PD)|F0:QMI.SD1), U5.2 (IO1)
/Mgmt MCU/MCU/QSPI.D2: U3.73 (QSPI.SD2(PU)|F0:QMI.SD2), U5.3 (IO2)
/Mgmt MCU/MCU/QSPI.D3: U3.70 (QSPI.SD3(PU)|F0:QMI.SD3), U5.7 (IO3)
/Mgmt MCU/MCU/QSPI.SCK: U3.71 (QSPI.SCK(PD)|F0:QMI.SCK), U5.6 (SCK)
/Mgmt MCU/MCU/QSPI.~CS: U3.75 (QSPI.~SS²(PU)|F0:QMI.~CS0), U5.1 (~CS)
/Mgmt MCU/MCU/VCORE: C27.2, C29.2, C31.2, C218.2, L7.2, U3.10 (DVDD), U3.32 (DVDD), U3.51 (DVDD), U3.65 (VREG.FB)
/Mgmt MCU/MCU/VIO: C3.2, C5.2, C7.2, C9.2, C11.2, C13.2, C15.2, C17.2, C19.2, C21.2, C23.2, C25.2, C216.2, R157.2, U3.5 (IOVDD), U3.15 (IOVDD), U3.24 (IOVDD), U3.29 (IOVDD), U3.41 (IOVDD), U3.50 (IOVDD), U3.59 (ADC.AVDD), U3.60 (IOVDD), U3.64 (VREG.VIN), U3.68 (USB_OTP.VDD), U3.69 (QSPI.IOVDD), U3.76 (IOVDD), U5.8 (VCC)
/Mgmt MCU/MCU/_USB.D+: R11.3, U3.67 (USB.D+|USB)
/Mgmt MCU/MCU/_USB.D-: R11.4, U3.66 (USB.D-|USB)
/Real-Time MCU/MCU/QSPI.D0: U4.72 (QSPI.SD0(PD)|F0:QMI.SD0), U6.5 (IO0)
/Real-Time MCU/MCU/QSPI.D1: U4.74 (QSPI.SD1²(PD)|F0:QMI.SD1), U6.2 (IO1)
/Real-Time MCU/MCU/QSPI.D2: U4.73 (QSPI.SD2(PU)|F0:QMI.SD2), U6.3 (IO2)
/Real-Time MCU/MCU/QSPI.D3: U4.70 (QSPI.SD3(PU)|F0:QMI.SD3), U6.7 (IO3)
/Real-Time MCU/MCU/QSPI.SCK: U4.71 (QSPI.SCK(PD)|F0:QMI.SCK), U6.6 (SCK)
/Real-Time MCU/MCU/QSPI.~CS: U4.75 (QSPI.~SS²(PU)|F0:QMI.~CS0), U6.1 (~CS)
/Real-Time MCU/MCU/VCORE: C28.2, C30.2, C32.2, C219.2, L8.2, U4.10 (DVDD), U4.32 (DVDD), U4.51 (DVDD), U4.65 (VREG.FB)
/Real-Time MCU/MCU/VIO: C4.2, C6.2, C8.2, C10.2, C12.2, C14.2, C16.2, C18.2, C20.2, C22.2, C24.2, C26.2, C217.2, R158.2, U4.5 (IOVDD), U4.15 (IOVDD), U4.24 (IOVDD), U4.29 (IOVDD), U4.41 (IOVDD), U4.50 (IOVDD), U4.59 (ADC.AVDD), U4.60 (IOVDD), U4.64 (VREG.VIN), U4.68 (USB_OTP.VDD), U4.69 (QSPI.IOVDD), U4.76 (IOVDD), U6.8 (VCC)
/Real-Time MCU/MCU/_USB.D+: R12.3, U4.67 (USB.D+|USB)
/Real-Time MCU/MCU/_USB.D-: R12.4, U4.66 (USB.D-|USB)
/Real-Time MCU/RTIO.AIO0: R46.4, U4.49 (GPIO40~(PD)|F3:I2C0.SDA)
/Real-Time MCU/RTIO.AIO1: R46.3, U4.52 (GPIO41~(PD)|F2:UART1.RX)
/Real-Time MCU/RTIO.AIO2: R46.2, U4.53 (GPIO42~(PD)|ADC2)
/Real-Time MCU/RTIO.AIO3: R46.1, U4.54 (GPIO43~(PD)|ADC3)
/Real-Time MCU/RTIO.AIO4: R44.4, U4.55 (GPIO44~(PD)|F2:UART0.TX)
/Real-Time MCU/RTIO.AIO5: R44.3, U4.56 (GPIO45~(PD)|F2:UART0.RX)
/Real-Time MCU/RTIO.AIO6: R44.2, U4.57 (GPIO46~(PD)|ADC6)
/Real-Time MCU/RTIO.AIO7: R44.1, U4.58 (GPIO47~(PD)|ADC7)
/Real-Time MCU/RTIO.DIO0: R47.4, U4.11 (GPIO12¹(PD)|GPIO)
/Real-Time MCU/RTIO.DIO1: R47.3, U4.12 (GPIO13¹(PD)|GPIO)
/Real-Time MCU/RTIO.DIO2: R47.2, U4.13 (GPIO14¹(PD)|GPIO)
/Real-Time MCU/RTIO.DIO3: R47.1, U4.14 (GPIO15¹(PD)|GPIO)
/Real-Time MCU/RTIO.DIO4: R45.4, U4.20 (GPIO20¹(PD)|GPIO)
/Real-Time MCU/RTIO.DIO5: R45.3, U4.21 (GPIO21¹(PD)|GPIO)
/Real-Time MCU/RTIO.DIO6: R45.2, U4.22 (GPIO22¹(PD)|GPIO)
/Real-Time MCU/RTIO.DIO7: R45.1, U4.23 (GPIO23¹(PD)|GPIO)
/USB ports/_USB3HIGH.SSTX+: C36.1, D12.1, J3.18 (TOP_SSTX+)
/USB ports/_USB3HIGH.SSTX-: C35.1, D12.2, J3.17 (TOP_SSTX-)
/USB ports/_USB3LOW.SSTX+: C34.1, D11.1, J3.9 (BOT_SSTX+)
/USB ports/_USB3LOW.SSTX-: C33.1, D11.2, J3.8 (BOT_SSTX-)
AV3P3: C90.2, C91.2, C92.2, C221.2, C223.2, J24.1, R64.1, R142.2, R166.1, R167.1, U11.9 (VD), U11.10 (VL), U23.1 (VCC1), U24.8 (VCC2)
AV5: C88.2, C89.2, C112.2, C119.2, C120.2, C133.2, C134.2, C140.2, C155.2, C156.2, C157.2, C175.2, C176.2, C177.2, C178.2, D19.2 (C), D20.2 (C), D21.2 (C), D22.2 (C), J23.1, L3.2, R106.1, R108.1, U11.20 (VA), U15.3 (V+), U16.3 (V+), U17.3 (V+), U18.3 (V+)
AVSS: C88.1, C89.1, C93.1, C94.2 (-), C95.1, C117.1, C118.2, C119.1, C120.1, C121.1, C125.1, C126.2, C128.2, C129.1, C130.1, C133.1, C134.1, C135.2, C136.1, C139.2, C140.1, C141.1, C144.2, C145.1, C146.2, C147.1, C148.1, C151.2, C152.1, C155.1, C156.1, C157.1, C158.1, C169.1, C171.1, C175.1, C176.1, C177.1, C178.1, D19.1 (A), D20.1 (A), D21.1 (A), D22.1 (A), J4.1, J4.G, J4.S, J5.1, J5.G, J5.S, J12.G, J12.TB, J12.TT, R63.1, R107.2, R109.2, R114.1, R115.1, R116.1, R117.1, R118.1, R119.1, R120.1, R121.1, U11.21 (AGND), U15.6 (V-), U16.6 (V-), U17.6 (V-), U18.6 (V-)
EARTH: C1.2, MNT1.1, R1.1
unnamed: C39.2, R15.2, X1.1
unnamed: C40.2, R16.2, X2.1
unnamed: C49.2, R34.2, R36.2, R38.2, R40.2
unnamed: C50.2, R35.2, R37.2, R39.2, R41.2
unnamed: C51.2, T1.6, T5.6, T9.6, T13.6
unnamed: C52.2, T2.6, T6.6, T10.6, T14.6
unnamed: C93.2, C94.1 (+), U11.22 (FILT+)
unnamed: C167.1, C168.1, C169.2
unnamed: C170.1, C171.2, C172.1
unnamed: C180.2, C181.2, C182.2, C185.2, L4.2, R126.1, R131.1
unnamed: C183.2, R128.2
unnamed: C190.2, R135.2
unnamed: C192.2, C193.2, C194.2, C195.2, L5.2, R136.1, R138.1
unnamed: C204.2, R152.2
unnamed: D1.C, R21.2
unnamed: D2.C, R22.2
unnamed: D3.C, R23.2
unnamed: D4.A, R42.1
unnamed: D5.A, R43.1
unnamed: D6.1, J15.13, R46.8
unnamed: D6.2, J15.16, R46.7
unnamed: D6.4, J15.19, R46.6
unnamed: D6.5, J15.22, R46.5
unnamed: D7.1, J15.1, R44.8
unnamed: D7.2, J15.4, R44.7
unnamed: D7.4, J15.7, R44.6
unnamed: D7.5, J15.10, R44.5
unnamed: D8.1, J16.22, R47.5
unnamed: D8.2, J16.19, R47.6
unnamed: D8.4, J16.16, R47.7
unnamed: D8.5, J16.13, R47.8
unnamed: D9.1, J16.10, R45.5
unnamed: D9.2, J16.7, R45.6
unnamed: D9.4, J16.4, R45.7
unnamed: D9.5, J16.1, R45.8
unnamed: D17.2 (A), J10.5 (CSINK), U10.2 (C)
unnamed: D17.1 (C), R51.2, U10.1 (A)
unnamed: D18.1 (C), J1.18 (5V), R58.1, R60.1, R62.1
unnamed: D23.C, R132.2
unnamed: D24.C, R139.2
unnamed: D25.2 (A), L6.2, U21.13 (SW), U21.14 (SW)
unnamed: D26.C, R156.2
unnamed: D16.5, J1.13 (CEC)
unnamed: D16.4, J1.15 (DDC.CLK), Q2.3 (D), R58.2
unnamed: D16.2, J1.16 (DDC.DATA), Q3.3 (D), R60.2
unnamed: D16.1, J1.19 (HotPlugDetect), Q4.3 (D), R62.2
unnamed: J1.0 (SHD), R50.2
unnamed: J2.9 (SHD), R48.2
unnamed: J3.19 (SHD), R49.2
unnamed: J8.AL (LEDL_A), R31.2
unnamed: J8.CL (LEDL_C), U8.25 (LED2)
unnamed: J8.AR (LEDR_A), R29.2
unnamed: J8.CR (LEDR_C), U8.26 (LED1)
unnamed: J8.SH (SHD), R33.2
unnamed: J9.AL (LEDL_A), R30.2
unnamed: J9.CL (LEDL_C), U7.25 (LED2)
unnamed: J9.AR (LEDR_A), R28.2
unnamed: J9.CR (LEDR_C), U7.26 (LED1)
unnamed: J9.SH (SHD), R32.2
unnamed: J10.4 (CSRC), R51.1
unnamed: C85.2, J10.G (GND)
unnamed: C86.2, J10.2 (SHIELD)
unnamed: J11.4 (CSINK), R53.1
unnamed: J11.5 (CSRC), R52.1
unnamed: J11.2 (GND), J11.G (GND), R54.2
unnamed: J13.69 (CFG1), R13.2, R14.1
unnamed: J13.10 (~LED1), R21.1
unnamed: J19.6 (~LED1), R22.1
unnamed: J19.16 (~LED2), R23.1
unnamed: J26.2, R124.2, R125.2
unnamed: JMP3.2, R122.2, R123.2
unnamed: Q1.3 (D), R55.1, R55.2, R55.3, R55.4, R56.1, R56.2, R56.3, R56.4
unnamed: Q5.3 (D), R132.1
unnamed: Q5.1 (G), R141.2, U19.5 (PG)
unnamed: Q6.3 (D), R139.1
unnamed: Q6.1 (G), R140.2, U20.5 (PG)
unnamed: Q7.3 (D), R156.1
unnamed: Q7.1 (G), R155.2
unnamed: R34.1, T1.3
unnamed: R35.1, T2.3
unnamed: R36.1, T5.3
unnamed: R37.1, T6.3
unnamed: R38.1, T9.3
unnamed: R39.1, T10.3
unnamed: R40.1, T13.3
unnamed: R41.1, T14.3
unnamed: U1.250 (VIN), U1.251 (VIN), U1.252 (VIN), U1.253 (VIN), U1.254 (VIN), U1.255 (VIN), U1.256 (VIN), U1.257 (VIN), U1.258 (VIN), U1.259 (VIN), U1.260 (VIN)
unnamed: C2.2, U2.8 (VCC)
unnamed: C214.2, R157.1, U3.61 (VREG.AVDD)
unnamed: L7.1, U3.63 (VREG.LX)
unnamed: C37.2, U3.30 (XIN), X1.3
unnamed: R15.1, U3.31 (XOUT)
unnamed: C215.2, R158.1, U4.61 (VREG.AVDD)
unnamed: L8.1, U4.63 (VREG.LX)
unnamed: C38.2, U4.30 (XIN), X2.3
unnamed: R16.1, U4.31 (XOUT)
unnamed: C74.2, R24.2, U7.28 (CKXTAL1), X3.3
unnamed: C73.2, R24.1, U7.29 (CKXTAL2), X3.1
unnamed: D4.C, U7.27 (LED0)
unnamed: R26.2, U7.31 (RSET)
unnamed: R19.1, U7.20 (~ISOLATE)
unnamed: C76.2, R25.2, U8.28 (CKXTAL1), X4.3
unnamed: C75.2, R25.1, U8.29 (CKXTAL2), X4.1
unnamed: D5.C, U8.27 (LED0)
unnamed: R27.2, U8.31 (RSET)
unnamed: R20.1, U8.20 (~ISOLATE)
unnamed: U9.15 (3.3V), U9.46 (3.3V), U9.50 (3.3V)
unnamed: R64.2, R65.1, U11.13 (AD0)
unnamed: C97.2, U11.2 (XTI), X5.3
unnamed: C96.2, U11.1 (XTO), X5.1
unnamed: C116.2, L2.2, U12.3 (VIN+)
unnamed: C115.2, L1.1, U12.8 (VOUT+)
unnamed: R66.2, R67.1, U13.5 (EN)
unnamed: R68.2, R69.1, U13.8 (FB)
unnamed: C98.2, C111.2, C113.2, L3.1, R68.1, U13.1 (OUT)
unnamed: R70.2, R71.1, U14.5 (EN)
unnamed: R72.2, R73.1, U14.8 (FB)
unnamed: C103.2, C114.2, R72.1, R142.1, U14.1 (OUT)
unnamed: C179.1, U19.6 (BST)
unnamed: C184.2, R128.1, U19.4 (COMP)
unnamed: R129.2, R130.1, U19.2 (EN)
unnamed: C185.1, R126.2, R127.1, U19.3 (FB)
unnamed: C179.2, L4.1, U19.7 (NC(SW)), U19.9 (SW)
unnamed: C189.1, U20.6 (BST)
unnamed: C191.2, R135.1, U20.4 (COMP)
unnamed: R133.2, R134.1, U20.2 (EN)
unnamed: C195.1, R136.2, R137.1, U20.3 (FB)
unnamed: C189.2, L5.1, U20.7 (NC(SW)), U20.9 (SW)
unnamed: C203.2, R152.1, U21.8 (COMP)
unnamed: R148.2, R149.1, U21.6 (EN_UVLO_SYNC)
unnamed: R153.2, R154.1, U21.9 (FB)
unnamed: R150.1, U21.11 (MODE)
unnamed: R151.1, U21.5 (RT)
unnamed: C202.2, U21.10 (SS)
unnamed: C201.2, U21.2 (VCC)
unnamed: R143.2, R144.1, U22.5 (EN)
unnamed: C199.1, R145.2, R146.1, U22.2 (FB)
unnamed: R159.1, U23.2 (INA)
unnamed: R160.1, U23.3 (INB)
unnamed: R161.1, U23.4 (INC)
unnamed: R162.1, U23.5 (IND)
unnamed: R163.1, U23.6 (OUTE)
V3P3: C220.2, C222.2, D24.A, J21.1, R138.2, R140.1, R164.1, R165.1, U23.16 (VCC2), U24.1 (VCC1)
V5: D18.2 (A), D23.A, J20.1, R131.2, R141.1
V12: C99.2, C110.1 (+), C186.2, C187.1 (+), C188.2, J14.1, L2.1, R129.1, R133.1, U19.1 (VIN), U20.1 (VIN)
V12ISO: C100.2, C101.2, C102.2, C104.1 (+), C196.2, C197.2, C198.2, C200.2, J22.1, L1.2, L6.1, R66.1, R70.1, R148.1, U13.4 (IN), U14.4 (IN), U21.3 (BIAS)
V50: C205.2, C206.1 (+), C207.2, D25.1 (C), R143.1, R153.1, U22.8 (IN)
VIO: Q2.1 (G), Q3.1 (G), Q4.1 (G), R57.1, R59.1, R61.1
VM2: D1.A, D2.A, D3.A, J13.2 (V3P3), J13.4 (V3P3), J13.12 (V3P3), J13.14 (V3P3), J13.16 (V3P3), J13.18 (V3P3), J13.70 (V3P3), J13.72 (V3P3), J13.74 (V3P3), J19.2 (V3P3), J19.4 (V3P3), J19.72 (V3P3), J19.74 (V3P3), R13.1
VMIDI: C87.2, R53.2, U10.6 (VCC)
VPHANTOM: D26.A, J26.1, JMP3.1, R147.2, R155.1
VRTIO: J15.2, J15.5, J15.8, J15.11, J15.14, J15.17, J15.20, J15.23, J16.2, J16.5, J16.8, J16.11, J16.14, J16.17, J16.20, J16.23
VSS: C1.1, C2.1, C3.1, C4.1, C5.1, C6.1, C7.1, C8.1, C9.1, C10.1, C11.1, C12.1, C13.1, C14.1, C15.1, C16.1, C17.1, C18.1, C19.1, C20.1, C21.1, C22.1, C23.1, C24.1, C25.1, C26.1, C27.1, C28.1, C29.1, C30.1, C31.1, C32.1, C37.1, C38.1, C39.1, C40.1, C49.1, C50.1, C51.1, C52.1, C53.1, C54.1, C55.1, C56.1, C57.1, C58.1, C59.1, C60.1, C61.1, C62.1, C63.1, C64.1, C65.1, C66.1, C67.1, C68.1, C69.1, C70.1, C71.1, C72.1, C73.1, C74.1, C75.1, C76.1, C85.1, C86.1, C87.1, C99.1, C105.2, C106.2, C107.2, C108.2, C109.2, C110.2 (-), C116.1, C180.1, C181.1, C182.1, C183.1, C184.1, C186.1, C187.2 (-), C188.1, C190.1, C191.1, C192.1, C193.1, C194.1, C210.2, C211.2, C212.2, C213.2, C214.1, C215.1, C216.1, C217.1, C218.1, C219.1, C220.1, C222.1, D6.3, D7.3, D8.3, D9.3, D10.3, D11.3, D12.3, D13.3, D14.3, D15.3, D16.3, J1.2 (TMDS.D2SHD), J1.5 (TMDS.D1SHD), J1.8 (TMDS.D0SHD), J1.11 (TMDS.CLKSHD), J1.17 (GND), J2.4 (TOP_GND), J2.8 (BOT_GND), J3.4 (BOT_GND)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

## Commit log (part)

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2026-02-08 initial commit added lattepanda kicad lib added top-arch diagram (70% done)
2026-02-08 ignored drawio temp files
2026-02-11 added audio section to top-arch diagram
2026-02-11 added reference documentation
2026-02-12 added notes after review meeting to top arch diagram
2026-02-15 added last? details on top-arch diagram
2026-02-18 added reference design for mic preamp and phantom psu
2026-02-18 moved thatmicpre submodule to ref
2026-02-19 added audio reference circuits
2026-02-19 started pwr tree diagram added appnote for phantom power supply
2026-02-22 added lattepanda model and footprint some small modif on symbol so it is normalized
2026-02-22 added skeleton schematic and some pcb placement
2026-02-22 ignore caches files of kicad
2026-02-26 added usb, hdmi and combo xlrtrs connectors resized pcb for something realistic (still wip)
2026-02-28 added RP2350's crystals added 8p8c shielded with led connector (both the same for now)
2026-03-02 added all remaining connectors (only missing M.2 now)
2026-03-05 Added lots to sch and pcb: eth passive, audio codec, midi, teensy Corrected and added support for M.2
2026-03-05 added ref doc for cs4272 audio interface based on teensy
2026-03-07 lots of work done all around
2026-03-08 added power stuff revised M.2 for higher model and added m.2 mounts added power tap terminals
2026-03-09 Lots of routing done power blocks intra-routing mostly done rp2350 routing mostly done some label cleanup
2026-03-09 added v50 regulator design from wbdesign
2026-03-10 added i2s/i2c isolation for audio section
2026-03-10 reshowed the hdmi cable in 3d render
2026-03-10 lots of routing (diff, buses, power) done optimised buffer out
2026-03-10 added encoder, more routing done, pinout doc added
2026-03-11 added display flatflex conn
2026-03-11 corrected display conn footprint
2026-03-11 lcd control circuit added fan interface added rgba output pinout for management mcu accessories done
2026-03-12 added todos following review
2026-03-13 most of board control signals added, routed and defined
2026-03-14 added expansion port and more ctl to rp2350s routing much progress
2026-03-16 more routing/placement done added 5v load switch 1A each added second fan circuit redone all diffpair routing following new stackup calc added all (?) missing connectors to unused pins
2026-03-17 added monitor amp with volume knob continue routing all around
2026-03-17 last sprint almost done, most routing done
2026-03-18 all routed, review starting
2026-03-19 finished adding mpn,mfg to all parts, finished routing placement
2026-03-19 DRC passing
2026-03-20 final design pass for A0 done release artifact created and sent to quote
2026-03-21 updated to kicad 10 file format
